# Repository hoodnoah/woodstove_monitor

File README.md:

# Woodstove Monitor

A Rust-based temperature monitoring system for woodstoves using an Arduino Nano ESP32 and a MAX31855 thermocouple sensor. The device reads temperature data and publishes it to MQTT for remote monitoring.

## Features

- **Temperature Monitoring**: Reads thermocouple data via MAX31855 SPI sensor
- **WiFi Connectivity**: Connects to WiFi networks for remote access
- **MQTT Publishing**: Publishes temperature readings and stove state to an MQTT broker
- **State Machine**: Tracks woodstove burn state based on temperature readings
- **Low Power**: Optimized for minimal resource usage on embedded systems

## Hardware

- Arduino Nano ESP32 (ESP32-S3)
- MAX31855 Thermocouple Amplifier (SPI interface)
- Status LED (GPIO8)
- WiFi antenna

## Project Structure

- `monitor/`: Main ESP32 application (firmware)
  - `main.rs`: Entry point, hardware setup, main loop
  - `mqtt.rs`: MQTT client and publishing logic
  - `wifi.rs`: WiFi connectivity
- `woodstove_lib/`: Shared library with core logic
  - `state_machine.rs`: Stove state tracking
  - `sensor.rs`: Sensor abstractions
  - `temperature.rs`: Temperature value types

## Setup

### Prerequisites

See [SETUP.md](SETUP.md) for detailed platform-specific installation instructions.

**Quick setup:**

1. Install system dependencies (cmake, ninja, LLVM, Python 3.12, etc. - see SETUP.md)
2. Set required environment variables (see SETUP.md)
3. Install ESP tooling:
   ```bash
   just check-deps  # Verify dependencies
   just setup       # Install ESP tools (one-time)
   source ~/export-esp.sh  # Load ESP environment
   ```

### Configuration

Set environment variables for your WiFi and MQTT credentials:

```bash
export WIFI_SSID="your_ssid"
export WIFI_PASSWORD="your_password"
export MQTT_ENDPOINT="mqtt://broker.example.com"
export MQTT_USER="username"
export MQTT_PASS="password"
```

Alternatively, create a `.env` file in the `monitor/` directory.

## Building and Flashing

```bash
# Build release binary
just build

# Flash to device and monitor serial output
just flash

# Monitor only (if device is already flashed)
just monitor

# Clean build artifacts
just clean
```

## Development

```bash
# Test the shared library
just test-lib
```

## Resources

- [esp-rs Book](https://docs.espressif.com/projects/rust/book/)
- [esp-idf-svc Documentation](https://docs.rs/esp-idf-svc/)
- [MAX31855 Datasheet](https://datasheets.maximintegrated.com/en/ds/MAX31855.pdf)

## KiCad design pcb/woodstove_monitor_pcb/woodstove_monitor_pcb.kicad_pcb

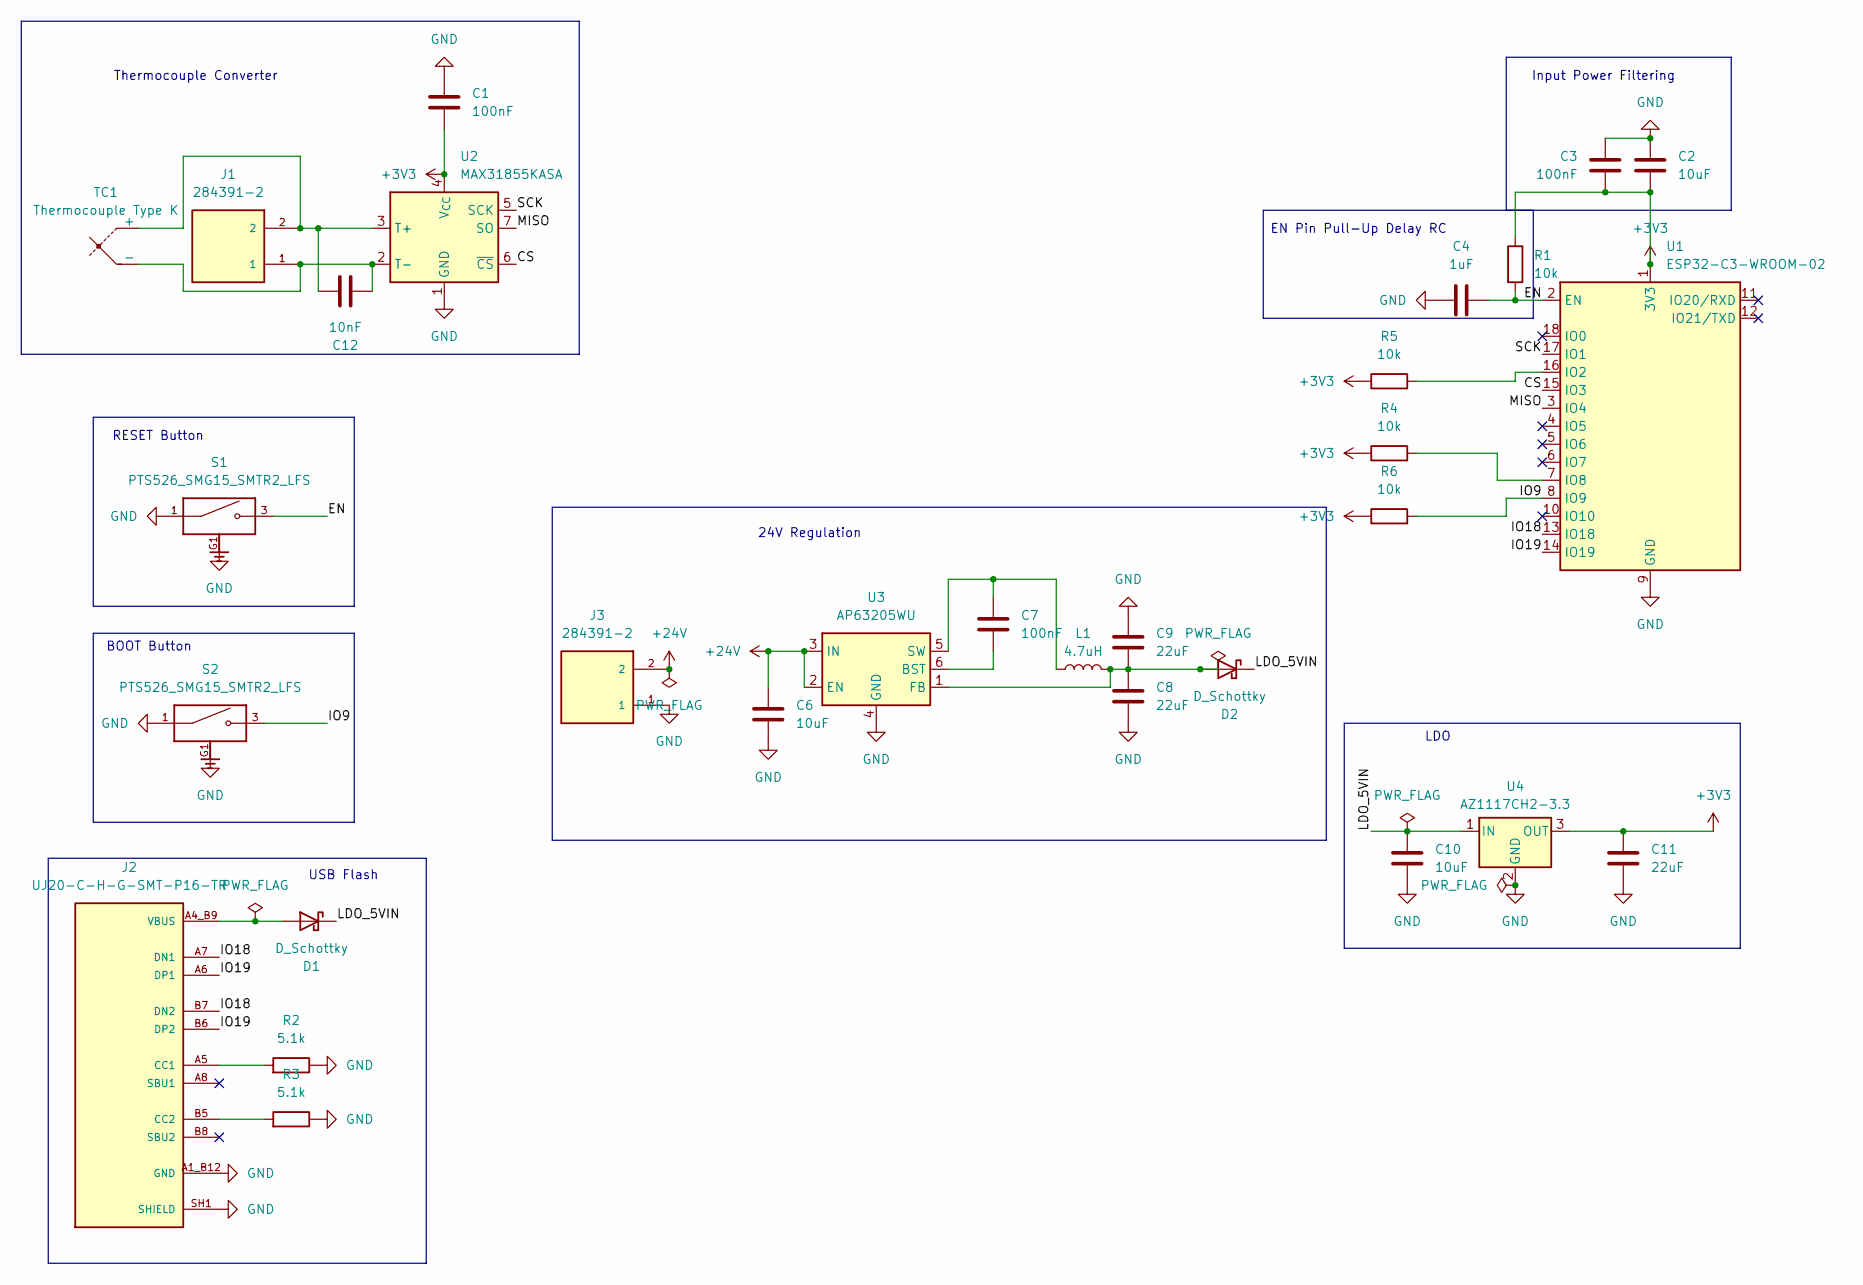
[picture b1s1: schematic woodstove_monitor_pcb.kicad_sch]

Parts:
C1, C3, C7: 100nF; C_0805_2012Metric; Mouser Part # 80-C0805C104M5RACLR
C2, C6, C10: 10uF; C_0805_2012Metric; Mouser Part # 187-CL21B106KPQNNNE
C4: 1uF; C_0805_2012Metric; Mouser Part # 80-C0805C105K3RACTM
C8, C9, C11: 22uF; C_0805_2012Metric; Mouser Part # 581-KAM21AT70J226MU
C12: 10nF; C_0805_2012Metric; Mouser Part # 80-C0805C103J5RACTM
D1, D2: D_Schottky; D_SOD-323; Mouser Part # 726-BAT60BE6359HTMA1
J1, J3: 284391-2; TE_284391-2; PARTREV C; Mouser Part # 571-284391-2
J2: UJ20-C-H-G-SMT-P16-TR; SAMESKY_UJ20-C-H-G-SMT-P16-TR; PARTREV 1.0; Mouser Part # 179-UJ20CHGSMTP16TR
L1: 4.7uH; L_Taiyo-Yuden_NR-50xx; Mouser Part # 963-NRS5020T4R7MMGJ
R1, R4, R5, R6: 10k; R_0805_2012Metric; Mouser Part # 303-0805S8J0103T5E
R2, R3: 5.1k; R_0805_2012Metric; Mouser Part # 660-SG73S2ATTD512J
S1, S2: PTS526_SMG15_SMTR2_LFS; SW_PTS526_SMG15_SMTR2_LFS; PARTREV 20 Nov 20; Mouser Part # 611-PTS526SMG15SMR2L
TC1: Thermocouple Type K
U1: ESP32-C3-WROOM-02; Mouser Part # 356-ESP32C3WROOM02N4; LCSC Part # C2934560
U2: MAX31855KASA; SOIC-8_3.9x4.9mm_P1.27mm; Mouser Part # 700-MAX31855KASA+
U3: AP63205WU; TSOT-23-6; Mouser Part # 621-AP63205WU-7
U4: AZ1117CH2-3.3; SOT-223-3_TabPin2; Mouser Part # 621-AZ1117CH2-33TRG1

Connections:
+3V3: C1.2, C2.2, C3.2, C11.1, R1.1, R4.1, R5.1, R6.1, U1.1 (3V3), U2.4 (V_{CC}), U4.3 (OUT)
+24V: C6.1, J3.2, U3.2 (EN), U3.3 (IN)
/CS: U1.15 (IO3), U2.6 (~CS)
/EN: C4.1, R1.2, S1.3, S1.4, U1.2 (EN)
/IO9: R6.2, S2.3, S2.4, U1.8 (IO9)
/IO18: J2.A7 (DN1), J2.B7 (DN2), U1.13 (IO18)
/IO19: J2.A6 (DP1), J2.B6 (DP2), U1.14 (IO19)
/LDO_5VIN: C10.1, D1.1 (K), D2.1 (K), U4.1 (IN)
/MISO: U1.3 (IO4), U2.7 (SO)
/SCK: U1.17 (IO1), U2.5 (SCK)
GND: C1.1, C2.1, C3.1, C4.2, C6.2, C8.2, C9.1, C10.2, C11.2, J2.A1_B12 (GND), J2.A12_B1 (GND), J2.SH1 (SHIELD), J2.SH2 (SHIELD), J2.SH3 (SHIELD), J2.SH4 (SHIELD), J3.1, R2.1, R3.1, S1.1, S1.2, S1.G1, S1.G2, S2.1, S2.2, S2.G1, S2.G2, U1.9 (GND), U1.19 (GND), U2.1 (GND), U3.4 (GND), U4.2 (GND)
unnamed: C8.1, C9.2, D2.2 (A), L1.2, U3.1 (FB)
unnamed: J2.A5 (CC1), R2.2
unnamed: J2.B5 (CC2), R3.2
unnamed: R5.2, U1.16 (IO2)
unnamed: R4.2, U1.7 (IO8)
unnamed: C12.2, J1.2, TC1.1 (+), U2.3 (T+)
unnamed: C12.1, J1.1, TC1.2 (-), U2.2 (T-)
unnamed: C7.1, U3.6 (BST)
unnamed: C7.2, L1.1, U3.5 (SW)
VBUS: D1.2 (A), J2.A4_B9 (VBUS), J2.A9_B4 (VBUS)

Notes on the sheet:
Input Power Filtering
BOOT Button
Thermocouple Converter
24V Regulation
USB Flash
RESET Button
EN Pin Pull-Up Delay RC
LDO

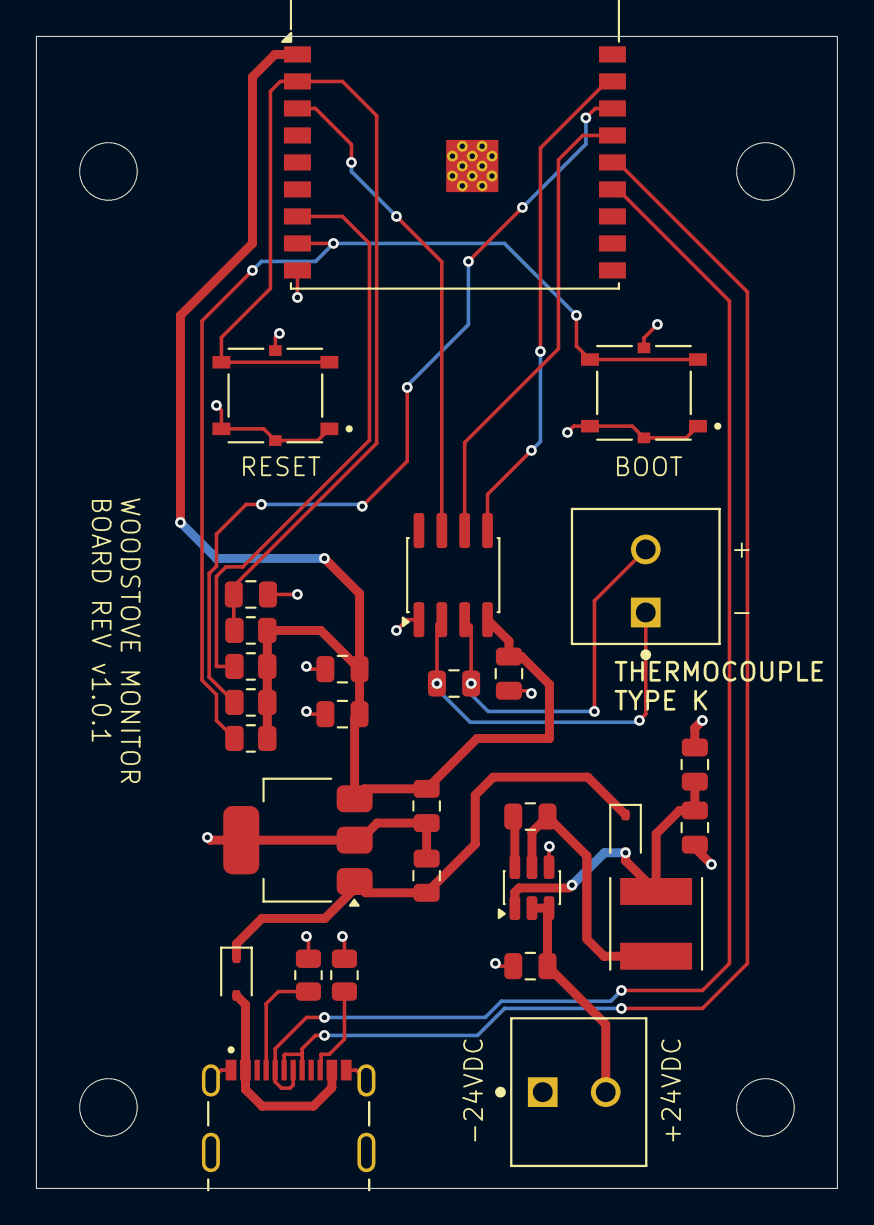
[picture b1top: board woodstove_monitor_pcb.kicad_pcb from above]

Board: 2 copper layers, 44.5 x 64.0 mm, 29 parts (0 on the bottom side), 21 nets.

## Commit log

2025-12-14 working initial setup w/ flake
2025-12-14 working flashing version
2025-12-14 update readme to reflect steps taken
2025-12-15 begin implementation of state machine w/ tdd
2025-12-15 implement EMA for calculating rate of change of temperature
2025-12-17 implement state classification, begin implementation of tests thereagainst
2025-12-22 separate lib and main workspaces, implement unit tests for state transitions
    separate workspaces, add unit tests for state transitions
2025-12-23 fix bugs, add boolean return to show true when state changes
2025-12-24 add dependency on MAX31855 crate for thermocouple driver
2025-12-25 implement utility types over temperature, rates of change, temperature deltas to prevent unit commingling; reimplement unit tests
    formalize unit types, refactor state_machine, some tests to make use of new types
    checkpoint
2025-12-26 rudimentary implementation of sensor functionality
2025-12-26 setup wifi, switch to arduino nano esp32 since wifi is broken on esp32c3
    checkpoint before switching to ardunio esp32
    setup wifi, switch to arduino nano esp32 since wifi is broken on esp32c3
2025-12-26 working mqtt
2025-12-27 add state machine, publishing of state/time_in_state to mqtt
2025-12-28 implement Display trait for BurnState enum
2025-12-28 factor mqtt commands, client out into utility struct
2025-12-29 factor wifi setup, connection out into a helper module
2026-01-04 fix overheat notification bug by adding overheat exit threshold
2026-01-04 add changelog
2026-01-25 fix crash when mqtt broker is down, reduce boilerplate
2026-01-25 cargo fix to remove unused imports
2026-01-25 add rust analyzer to flake
2026-01-25 add nil, nixd to flake
2026-01-25 fix rust-analyzer issues
2026-01-25 fix justfile to cd into directories as needed
2026-02-14 implement wifi reconnection logic following power outage exposing no reconnection logic
2026-02-14 abandon nix in favor of individual system instructions
2026-02-14 fix partition table issues in .cargo/config.toml, alter setup re: fish
2026-02-19 add linter workflow for gitea
2026-02-19 add manual run option for linting
2026-02-19 fix linter workflow to limit to lib
2026-02-19 fix clippy complaints
2026-03-02 v1 schematic
2026-03-02 remove zips
2026-03-13 update part no. for LDO; MUST BE H2 version, not H1
2026-03-19 update dummy pin, build config
2026-03-19 add config update functionality
